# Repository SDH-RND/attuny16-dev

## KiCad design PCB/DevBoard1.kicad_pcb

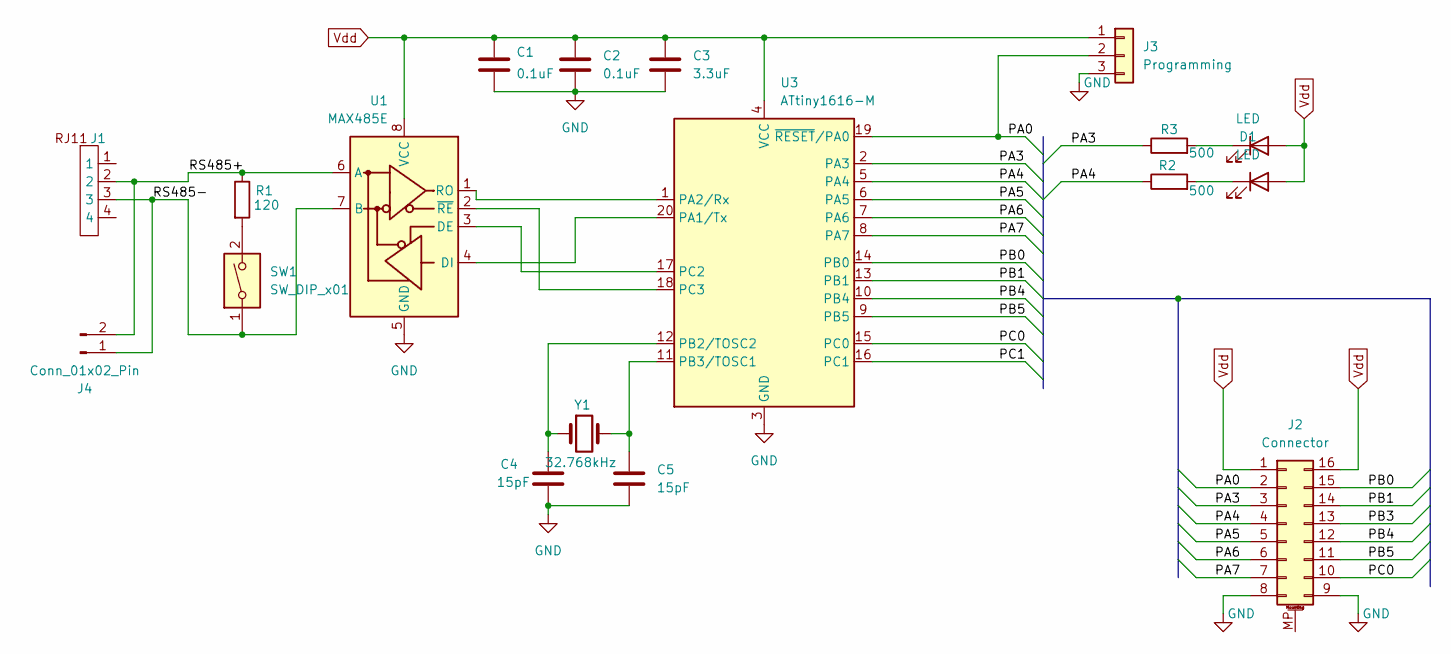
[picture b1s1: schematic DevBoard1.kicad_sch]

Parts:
C1, C2: 0.1uF; C_0402_1005Metric
C3: 3.3uF; C_1210_3225Metric
C4, C5: 15pF; C_0402_1005Metric
D1, D2: LED; LED_0805_2012Metric
J1: Molex4P4CVertical
J2: Connector; PinHeader_2x08_P2.54mm_Vertical
J3: Programming; PinHeader_1x03_P2.54mm_Vertical
J4: Conn_01x02_Pin; TerminalBlock_MaiXu_MX126-5.0-02P_1x02_P5.00mm
R1: 120; R_0402_1005Metric
R2, R3: 500; R_0603_1608Metric
SW1: SW_DIP_x01; SW_DIP_SPSTx01_Slide_6.7x4.1mm_W6.73mm_P2.54mm_LowProfile_J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; PartNumber C7527751
U1: MAX485E; SOIC-8_3.9x4.9mm_P1.27mm; Part Number C481667
U3: ATtiny1616-M; VQFN-20-1EP_3x3mm_P0.4mm_EP1.7x1.7mm; Part Number C507118
Y1: 32.768kHz; Crystal_SMD_2012-2Pin_2.0x1.2mm; Part Number C90943

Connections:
/PA0: J2.2, J3.2, U3.19 (~RESET/PA0)
/PA3: J2.3, R3.1, U3.2 (PA3)
/PA4: J2.4, R2.1, U3.5 (PA4)
/PA5: J2.5, U3.6 (PA5)
/PA6: J2.6, U3.7 (PA6)
/PA7: J2.7, U3.8 (PA7)
/PB0: J2.15, U3.14 (PB0)
/PB1: J2.14, U3.13 (PB1)
/PB3: J2.13
/PB4: J2.12, U3.10 (PB4)
/PB5: J2.11, U3.9 (PB5)
/PC0: J2.10, U3.15 (PC0)
/PC1: U3.16 (PC1)
/RS485+: J1.2, J4.2, R1.1, U1.6 (A)
/RS485-: J1.3, J4.1, SW1.1, U1.7 (B)
GND: C1.2, C2.2, C3.2, C4.2, C5.2, J2.8, J2.9, J3.3, U1.5 (GND), U3.3 (GND), U3.21 (GND)
unnamed: D1.1 (K), R2.2
unnamed: D2.1 (K), R3.2
unnamed: R1.2, SW1.2
unnamed: U1.3 (DE), U3.17 (PC2)
unnamed: U1.4 (DI), U3.20 (PA1/Tx)
unnamed: U1.1 (RO), U3.1 (PA2/Rx)
unnamed: U1.2 (~RE), U3.18 (PC3)
unnamed: C4.1, U3.12 (PB2/TOSC2), Y1.1
unnamed: C5.1, U3.11 (PB3/TOSC1), Y1.2
Vdd: C1.1, C2.1, C3.1, D1.2 (A), D2.2 (A), J2.1, J2.16, J3.1, U1.8 (VCC), U3.4 (VCC)

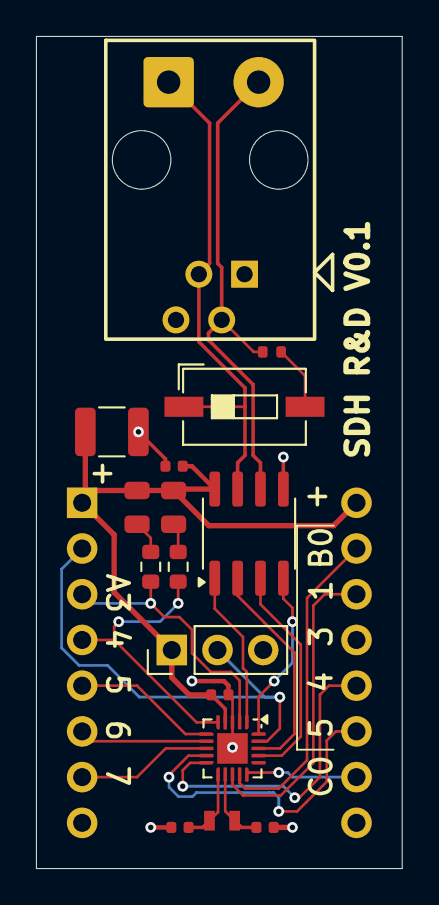
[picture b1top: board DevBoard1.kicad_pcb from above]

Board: 2 copper layers, 20.3 x 46.2 mm, 18 parts (0 on the bottom side), 24 nets.

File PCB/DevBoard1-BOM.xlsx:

Comment | Designator | Footprint | LCSC Part Number
0.1uF | C2,C1 | C_0402_1005Metric | C6955083
300 | R3,R2 | R_0603_1608Metric | C23025
120 | R1 | R_0402_1005Metric | C25140
Red | D1 | LED_0805_1005Metric | C84256
Green | D2 | LED_0805_1005Metric | C84257
15pF | C4,C5 | C_0402_1005Metric | C387970
32.768kHz | Y1 | Crystal_SMD_2012-2Pin_2.0x1.2mm | C90943
SW | SW1 | SW_DIP_SPSTx01_Slide_6.7x4.1mm_W6.73mm_P2.54mm_LowProfile_JPin | C7527751
ATtiny1616-M | U3 | VQFN-20-1EP_3x3mm_P0.4mm_EP1.7x1.7mm | C507118
MAX485E | U1 | SOIC-8_3.9x4.9mm_P1.27mm | C481667
3.3uF | C3 | C_1210_3225Metric | C397310

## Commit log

2025-05-06 initial commit KiCad files to git
